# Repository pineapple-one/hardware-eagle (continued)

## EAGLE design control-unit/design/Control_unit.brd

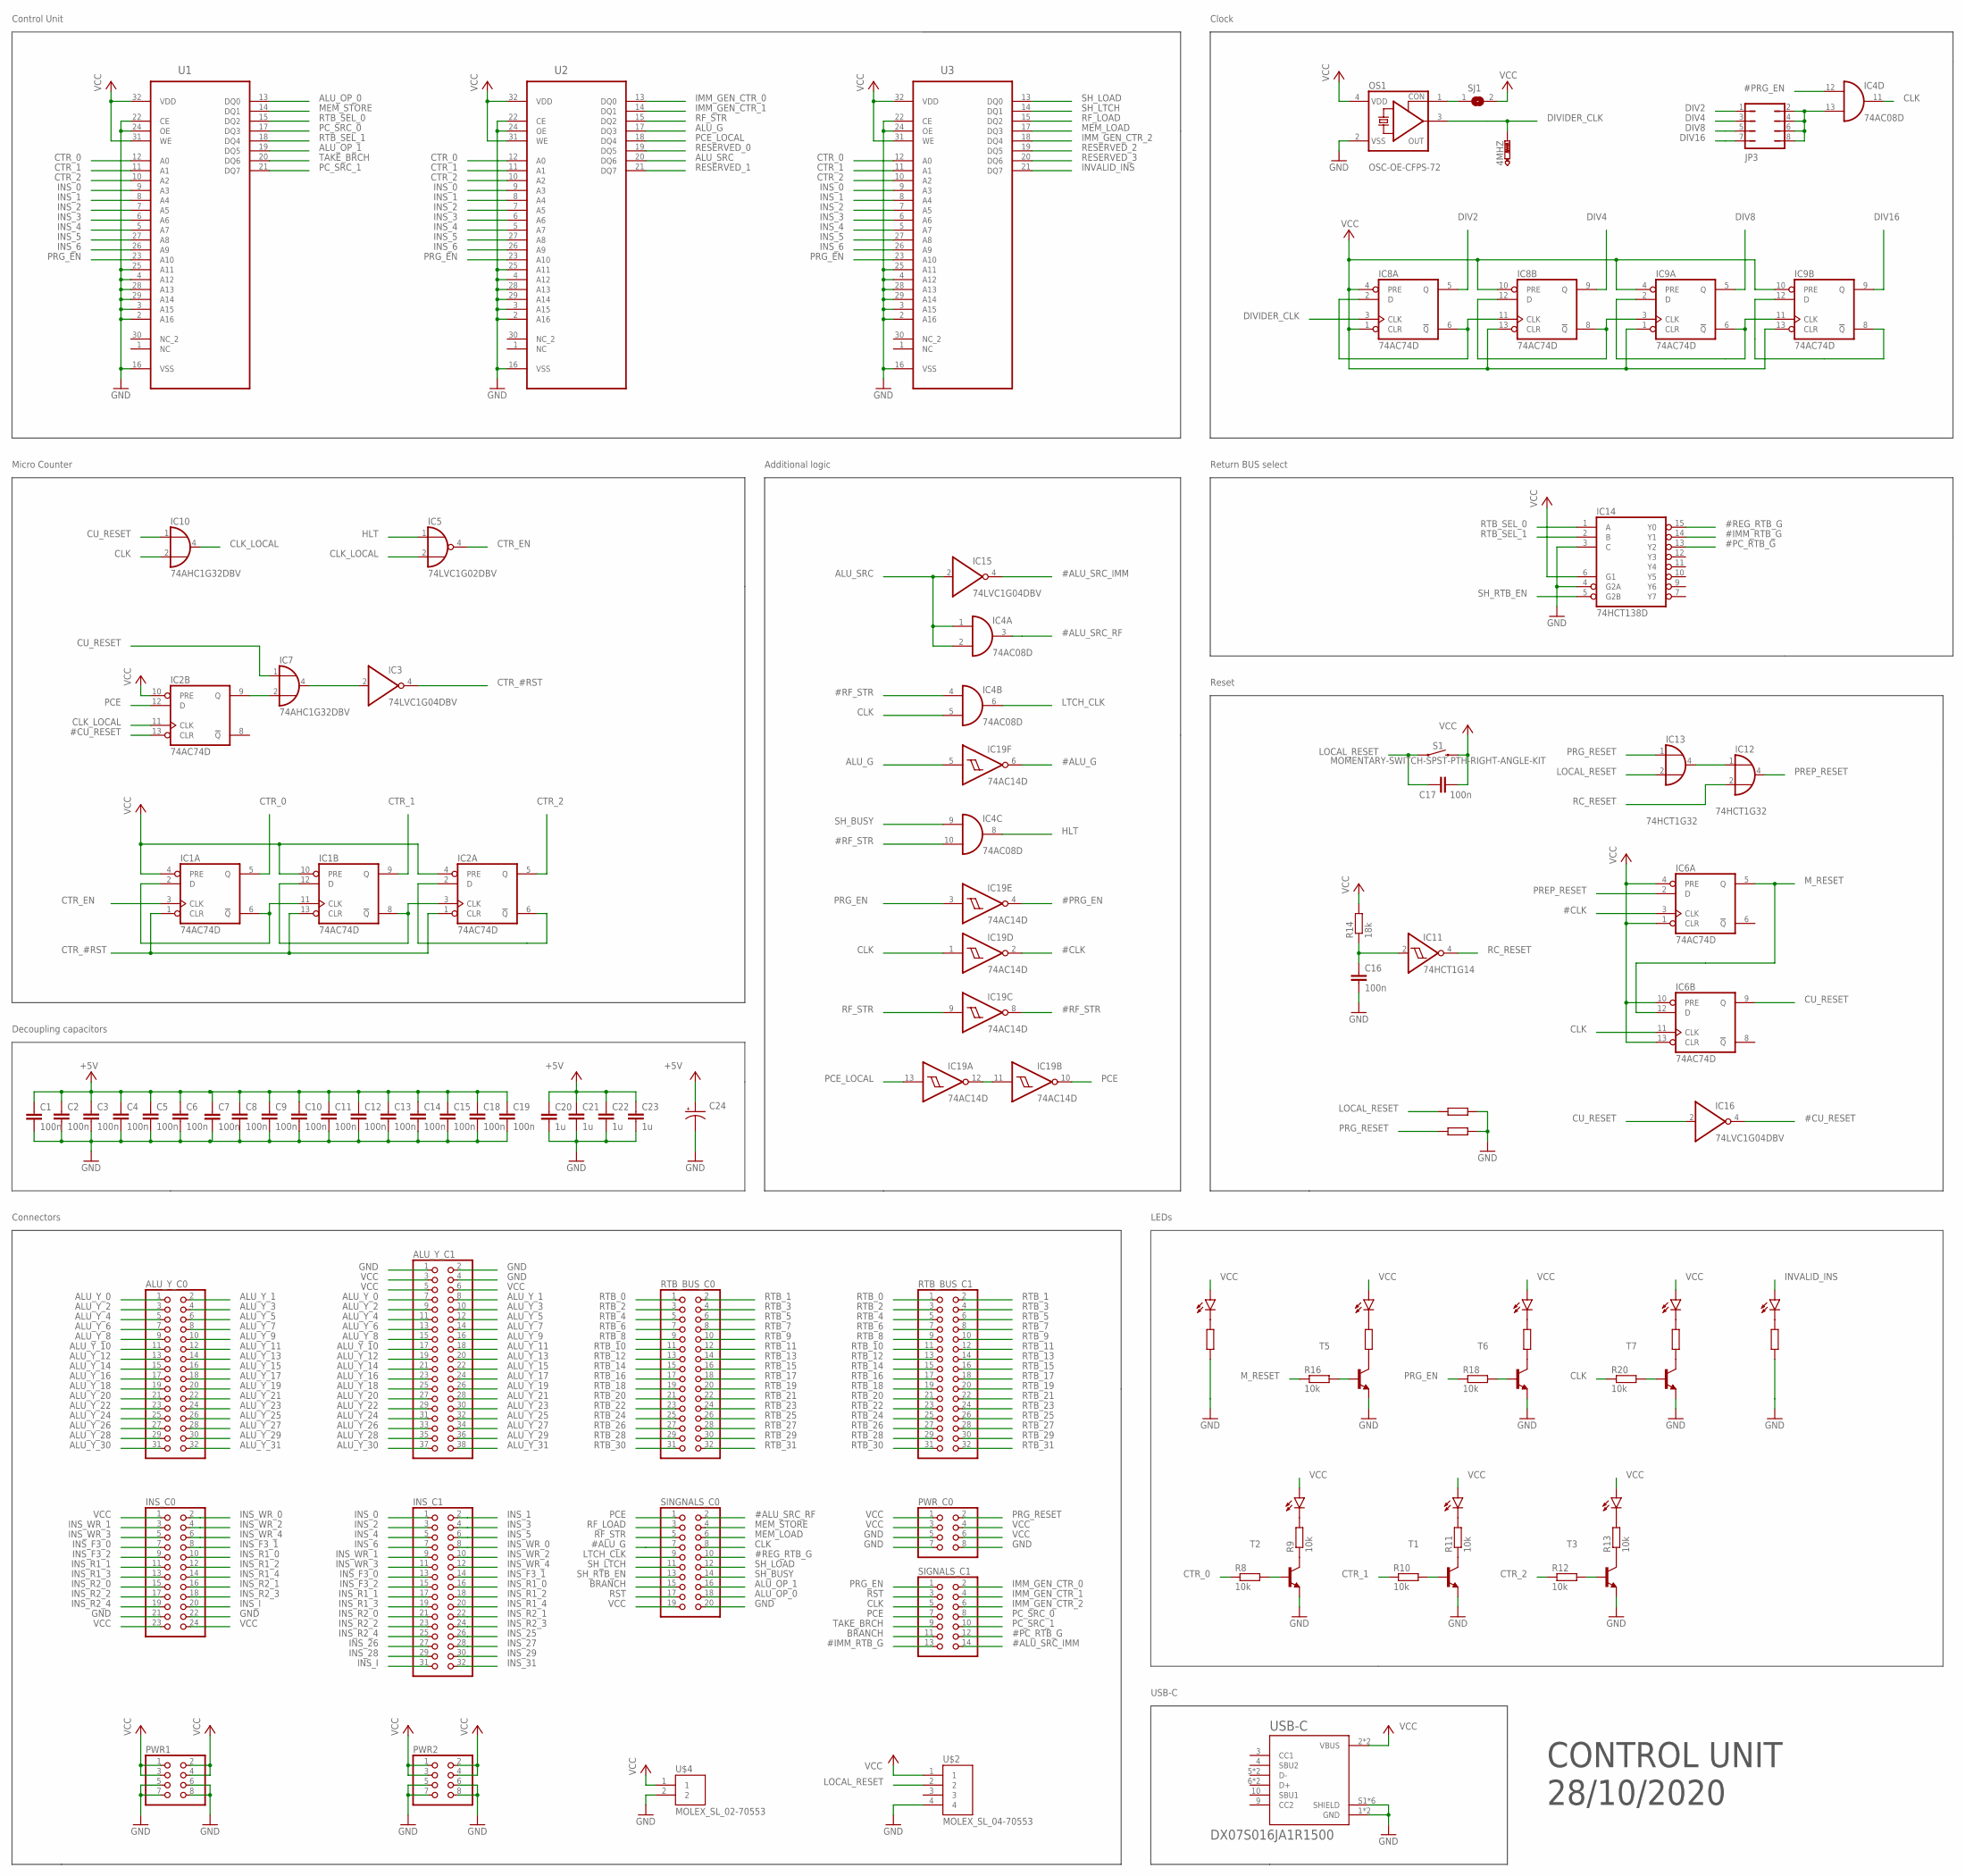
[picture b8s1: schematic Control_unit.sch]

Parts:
4MHZ: PTR1B2,54; B2,54
ALU_Y_C0: PINHD-2X16; 2X16
ALU_Y_C1: PINHD-2X19; 2X19
C1, C2, C3, C4, C5, C6, C7, C8, C9, C10, C11, C12, C13, C14, C15, C16, C17, C18, C19: 100n; C0805
C20, C21, C22, C23: 1u; C0805
C24: CAPACITOR-P153CLV-1010; 153CLV-1010
IC1, IC2, IC6, IC8, IC9: 74AC74D; SO14
IC3, IC15, IC16: 74LVC1G04DBV; SOT23-5
IC4: 74AC08D; SO14
IC5: 74LVC1G02DBV; SOT23-5
IC7, IC10: 74AHC1G32DBV; SOT23-5
IC11: 74HCT1G14; SOT23-5
IC12, IC13: 74HCT1G32; SOT23-5
IC14: 74HCT138D; SO16
IC19: 74AC14D; SO14
INS_C0: PINHD-2X12; 2X12
INS_C1: PINHD-2X16; 2X16
JP3: JP4Q
LED1, LED2, LED3, LED4, LED5, LED6, LED7, LED8: LEDSML0805; SML0805
OS1: OSC-OE-CFPS-72; 7.2X5.2-4-PAD
PWR1, PWR2: PINHD-2X4; 2X04
PWR_C0: PINHD-2X4; 2X04
R1, R2, R8, R9, R10, R11, R12, R13, R16, R18, R20: 10k; M0805
R3, R4, R5, R6, R7: 1k; M0805
R14: 18k; M0805
RTB_BUS_C0, RTB_BUS_C1: PINHD-2X16; 2X16
S1: MOMENTARY-SWITCH-SPST-PTH-RIGHT-ANGLE-KIT; TACTILE_SWITCH_PTH_RIGHT_ANGLE_KIT
SIGNALS_C1: PINHD-2X7; 2X07
SINGNALS_C0: PINHD-2X10; 2X10
SJ1: SJ
T1, T2, T3, T5, T6, T7: MMBT4401LT1-NPN-SOT23-BEC; SOT23-BEC
U1, U2, U3: SST39SF010A-70-4I-NHEPLCC32; S32
U$2: MOLEX_SL_04-70553; SL_70553_4
U$4: MOLEX_SL_02-70553; SL_70553_2
USB-C: DX07S016JA1R1500; JAE_DX07S016JA1R1500

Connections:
#ALU_G: IC19.6 (O), SINGNALS_C0.7
#ALU_SRC_IMM: IC15.4 (O), SIGNALS_C1.14
#ALU_SRC_RF: IC4.3 (O), SINGNALS_C0.2
#CLK: IC6.3 (CLK), IC19.2 (O)
#CU_RESET: IC2.13 (CLR), IC16.4 (O)
#IMM_RTB_G: IC14.14 (Y1), SIGNALS_C1.13
#PC_RTB_G: IC14.13 (Y2), SIGNALS_C1.12
#PRG_EN: IC4.12 (I0), IC19.4 (O)
#REG_RTB_G: IC14.15 (Y0), SINGNALS_C0.10
#RF_STR: IC4.4 (I0), IC4.10 (I1), IC19.8 (O)
ALU_G: IC19.5 (I), U2.17 (DQ3)
ALU_OP_0: SINGNALS_C0.18, U1.13 (DQ0)
ALU_OP_1: SINGNALS_C0.16, U1.19 (DQ5)
ALU_SRC: IC4.1 (I0), IC4.2 (I1), IC15.2 (I), U2.20 (DQ6)
ALU_Y_0: ALU_Y_C0.1, ALU_Y_C1.7
ALU_Y_1: ALU_Y_C0.2, ALU_Y_C1.8
ALU_Y_2: ALU_Y_C0.3, ALU_Y_C1.9
ALU_Y_3: ALU_Y_C0.4, ALU_Y_C1.10
ALU_Y_4: ALU_Y_C0.5, ALU_Y_C1.11
ALU_Y_5: ALU_Y_C0.6, ALU_Y_C1.12
ALU_Y_6: ALU_Y_C0.7, ALU_Y_C1.13
ALU_Y_7: ALU_Y_C0.8, ALU_Y_C1.14
ALU_Y_8: ALU_Y_C0.9, ALU_Y_C1.15
ALU_Y_9: ALU_Y_C0.10, ALU_Y_C1.16
ALU_Y_10: ALU_Y_C0.11, ALU_Y_C1.17
ALU_Y_11: ALU_Y_C0.12, ALU_Y_C1.18
ALU_Y_12: ALU_Y_C0.13, ALU_Y_C1.19
ALU_Y_13: ALU_Y_C0.14, ALU_Y_C1.20
ALU_Y_14: ALU_Y_C0.15, ALU_Y_C1.21
ALU_Y_15: ALU_Y_C0.16, ALU_Y_C1.22
ALU_Y_16: ALU_Y_C0.17, ALU_Y_C1.23
ALU_Y_17: ALU_Y_C0.18, ALU_Y_C1.24
ALU_Y_18: ALU_Y_C0.19, ALU_Y_C1.25
ALU_Y_19: ALU_Y_C0.20, ALU_Y_C1.26
ALU_Y_20: ALU_Y_C0.21, ALU_Y_C1.27
ALU_Y_21: ALU_Y_C0.22, ALU_Y_C1.28
ALU_Y_22: ALU_Y_C0.23, ALU_Y_C1.29
ALU_Y_23: ALU_Y_C0.24, ALU_Y_C1.30
ALU_Y_24: ALU_Y_C0.25, ALU_Y_C1.31
ALU_Y_25: ALU_Y_C0.26, ALU_Y_C1.32
ALU_Y_26: ALU_Y_C0.27, ALU_Y_C1.33
ALU_Y_27: ALU_Y_C0.28, ALU_Y_C1.34
ALU_Y_28: ALU_Y_C0.29, ALU_Y_C1.35
ALU_Y_29: ALU_Y_C0.30, ALU_Y_C1.36
ALU_Y_30: ALU_Y_C0.31, ALU_Y_C1.37
ALU_Y_31: ALU_Y_C0.32, ALU_Y_C1.38
BRANCH: SIGNALS_C1.11, SINGNALS_C0.15
CLK: IC4.5 (I1), IC4.11 (O), IC6.11 (CLK), IC10.2 (I1), IC19.1 (I), R20.1, SIGNALS_C1.5, SINGNALS_C0.8
CLK_LOCAL: IC2.11 (CLK), IC5.2 (I1), IC10.4 (O)
CTR_0: IC1.5 (Q), R8.1, U1.12 (A0), U2.12 (A0), U3.12 (A0)
CTR_1: IC1.9 (Q), R10.1, U1.11 (A1), U2.11 (A1), U3.11 (A1)
CTR_2: IC2.5 (Q), R12.1, U1.10 (A2), U2.10 (A2), U3.10 (A2)
CTR_#RST: IC1.1 (CLR), IC1.13 (CLR), IC2.1 (CLR), IC3.4 (O)
CTR_EN: IC1.3 (CLK), IC5.4 (O)
CU_RESET: IC6.9 (Q), IC7.1 (I0), IC10.1 (I0), IC16.2 (I)
DIV2: IC8.5 (Q), JP3.1
DIV4: IC8.9 (Q), JP3.3
DIV8: IC9.5 (Q), JP3.5
DIV16: IC9.9 (Q), JP3.7
DIVIDER_CLK: 4MHZ.TP, IC8.3 (CLK), OS1.3 (OUT)
GND: ALU_Y_C1.1, ALU_Y_C1.2, ALU_Y_C1.4, C1.2, C2.2, C3.2, C4.2, C5.2, C6.2, C7.2, C8.2, C9.2, C10.2, C11.2, C12.2, C13.2, C14.2, C15.2, C16.2, C18.2, C19.2, C20.2, C21.2, C22.2, C23.2, C24.-, IC1.7 (GND), IC2.7 (GND), IC3.3 (GND), IC4.7 (GND), IC5.3 (GND), IC6.7 (GND), IC7.3 (GND), IC8.7 (GND), IC9.7 (GND), IC10.3 (GND), IC11.3 (GND), IC12.3 (GND), IC13.3 (GND), IC14.3 (C), IC14.4 (G2A), IC14.8 (GND), IC15.3 (GND), IC16.3 (GND), IC19.7 (GND), INS_C0.21, INS_C0.22, OS1.2 (VSS), PWR1.5, PWR1.6, PWR1.7, PWR1.8, PWR2.5, PWR2.6, PWR2.7, PWR2.8, PWR_C0.5, PWR_C0.7, PWR_C0.8, R1.1, R2.1, R3.1, R7.1, SINGNALS_C0.20, T1.E, T2.E, T3.E, T5.E, T6.E, T7.E, U1.2 (A16), U1.3 (A15), U1.4 (A12), U1.16 (VSS), U1.22 (CE), U1.24 (OE), U1.25 (A11), U1.28 (A13), U1.29 (A14), U2.2 (A16), U2.3 (A15), U2.4 (A12), U2.16 (VSS), U2.22 (CE), U2.24 (OE), U2.25 (A11), U2.28 (A13), U2.29 (A14), U3.2 (A16), U3.3 (A15), U3.4 (A12), U3.16 (VSS), U3.22 (CE), U3.24 (OE), U3.25 (A11), U3.28 (A13), U3.29 (A14), U$2.4, U$4.2, USB-C.1 (GND), USB-C.12 (GND), USB-C.S1 (SHIELD), USB-C.S2 (SHIELD), USB-C.S3 (SHIELD), USB-C.S4 (SHIELD), USB-C.S5 (SHIELD), USB-C.S6 (SHIELD)
HLT: IC4.8 (O), IC5.1 (I0)
IMM_GEN_CTR_0: SIGNALS_C1.2, U2.13 (DQ0)
IMM_GEN_CTR_1: SIGNALS_C1.4, U2.14 (DQ1)
IMM_GEN_CTR_2: SIGNALS_C1.6, U3.18 (DQ4)
INS_0: INS_C1.1, U1.9 (A3), U2.9 (A3), U3.9 (A3)
INS_1: INS_C1.2, U1.8 (A4), U2.8 (A4), U3.8 (A4)
INS_2: INS_C1.3, U1.7 (A5), U2.7 (A5), U3.7 (A5)
INS_3: INS_C1.4, U1.6 (A6), U2.6 (A6), U3.6 (A6)
INS_4: INS_C1.5, U1.5 (A7), U2.5 (A7), U3.5 (A7)
INS_5: INS_C1.6, U1.27 (A8), U2.27 (A8), U3.27 (A8)
INS_6: INS_C1.7, U1.26 (A9), U2.26 (A9), U3.26 (A9)
INS_25: INS_C1.26
INS_26: INS_C1.27
INS_27: INS_C1.28
INS_28: INS_C1.29
INS_29: INS_C1.30
INS_31: INS_C1.32
INS_F3_0: INS_C0.7, INS_C1.13
INS_F3_1: INS_C0.8, INS_C1.14
INS_F3_2: INS_C0.9, INS_C1.15
INS_I: INS_C0.20, INS_C1.31
INS_R1_0: INS_C0.10, INS_C1.16
INS_R1_1: INS_C0.11, INS_C1.17
INS_R1_2: INS_C0.12, INS_C1.18
INS_R1_3: INS_C0.13, INS_C1.19
INS_R1_4: INS_C0.14, INS_C1.20
INS_R2_0: INS_C0.15, INS_C1.21
INS_R2_1: INS_C0.16, INS_C1.22
INS_R2_2: INS_C0.17, INS_C1.23
INS_R2_3: INS_C0.18, INS_C1.24
INS_R2_4: INS_C0.19, INS_C1.25
INS_WR_0: INS_C0.2, INS_C1.8
INS_WR_1: INS_C0.3, INS_C1.9
INS_WR_2: INS_C0.4, INS_C1.10
INS_WR_3: INS_C0.5, INS_C1.11
INS_WR_4: INS_C0.6, INS_C1.12
INVALID_INS: LED5.A, U3.21 (DQ7)
LOCAL_RESET: C17.1, IC13.2 (I1), R1.2, S1.1, U$2.2
LTCH_CLK: IC4.6 (O), SINGNALS_C0.9
MEM_LOAD: SINGNALS_C0.6, U3.17 (DQ3)
MEM_STORE: SINGNALS_C0.4, U1.14 (DQ1)
M_RESET: IC6.5 (Q), IC6.12 (D), R16.1
unnamed: IC1.2 (D), IC1.6 (!Q), IC1.11 (CLK)
unnamed: IC12.1 (I0), IC13.4 (O)
unnamed: IC2.9 (Q), IC7.2 (I1)
unnamed: IC3.2 (I), IC7.4 (O)
unnamed: IC19.11 (I), IC19.12 (O)
unnamed: IC8.2 (D), IC8.6 (!Q), IC8.11 (CLK)
unnamed: IC1.8 (!Q), IC1.12 (D), IC2.3 (CLK)
unnamed: R4.1, T5.C
unnamed: IC2.2 (D), IC2.6 (!Q)
unnamed: R5.1, T6.C
unnamed: R6.1, T7.C
unnamed: LED1.C, R3.2
unnamed: R8.2, T2.B
unnamed: LED8.C, R9.2
unnamed: IC8.8 (!Q), IC8.12 (D), IC9.3 (CLK)
unnamed: LED2.C, R4.2
unnamed: LED3.C, R5.2
unnamed: R9.1, T2.C
unnamed: R10.2, T1.B
unnamed: LED6.C, R11.2
unnamed: R11.1, T1.C
unnamed: R12.2, T3.B
unnamed: LED7.C, R13.2
unnamed: R13.1, T3.C
unnamed: R16.2, T5.B
unnamed: LED4.C, R6.2
unnamed: LED5.C, R7.2
unnamed: R18.2, T6.B
unnamed: IC9.2 (D), IC9.6 (!Q), IC9.11 (CLK)
unnamed: IC9.8 (!Q), IC9.12 (D)
unnamed: R20.2, T7.B
unnamed: C16.1, IC11.2 (I), R14.1
unnamed: OS1.1 (CON), SJ1.1
unnamed: IC4.13 (I1), JP3.2, JP3.4, JP3.6, JP3.8
PCE: IC2.12 (D), IC19.10 (O), SIGNALS_C1.7, SINGNALS_C0.1
PCE_LOCAL: IC19.13 (I), U2.18 (DQ4)
PC_SRC_0: SIGNALS_C1.8, U1.17 (DQ3)
PC_SRC_1: SIGNALS_C1.10, U1.21 (DQ7)
PREP_RESET: IC6.2 (D), IC12.4 (O)
PRG_EN: IC19.3 (I), R18.1, SIGNALS_C1.1, U1.23 (A10), U2.23 (A10), U3.23 (A10)
PRG_RESET: IC13.1 (I0), PWR_C0.2, R2.2
RC_RESET: IC11.4 (O), IC12.2 (I1)
RESERVED_0: U2.19 (DQ5)
RESERVED_1: U2.21 (DQ7)
RESERVED_2: U3.19 (DQ5)
RESERVED_3: U3.20 (DQ6)
RF_LOAD: SINGNALS_C0.3, U3.15 (DQ2)
RF_STR: IC19.9 (I), SINGNALS_C0.5, U2.15 (DQ2)
RST: SIGNALS_C1.3, SINGNALS_C0.17
RTB_0: RTB_BUS_C0.1, RTB_BUS_C1.1
RTB_1: RTB_BUS_C0.2, RTB_BUS_C1.2
RTB_2: RTB_BUS_C0.3, RTB_BUS_C1.3
RTB_3: RTB_BUS_C0.4, RTB_BUS_C1.4
RTB_4: RTB_BUS_C0.5, RTB_BUS_C1.5
RTB_5: RTB_BUS_C0.6, RTB_BUS_C1.6
RTB_6: RTB_BUS_C0.7, RTB_BUS_C1.7
RTB_7: RTB_BUS_C0.8, RTB_BUS_C1.8
RTB_8: RTB_BUS_C0.9, RTB_BUS_C1.9
RTB_9: RTB_BUS_C0.10, RTB_BUS_C1.10
RTB_10: RTB_BUS_C0.11, RTB_BUS_C1.11
RTB_11: RTB_BUS_C0.12, RTB_BUS_C1.12
RTB_12: RTB_BUS_C0.13, RTB_BUS_C1.13
RTB_13: RTB_BUS_C0.14, RTB_BUS_C1.14
RTB_14: RTB_BUS_C0.15, RTB_BUS_C1.15
RTB_15: RTB_BUS_C0.16, RTB_BUS_C1.16
RTB_16: RTB_BUS_C0.17, RTB_BUS_C1.17
RTB_17: RTB_BUS_C0.18, RTB_BUS_C1.18
RTB_18: RTB_BUS_C0.19, RTB_BUS_C1.19
RTB_19: RTB_BUS_C0.20, RTB_BUS_C1.20
RTB_20: RTB_BUS_C0.21, RTB_BUS_C1.21
RTB_21: RTB_BUS_C0.22, RTB_BUS_C1.22
RTB_22: RTB_BUS_C0.23, RTB_BUS_C1.23
RTB_23: RTB_BUS_C0.24, RTB_BUS_C1.24
RTB_24: RTB_BUS_C0.25, RTB_BUS_C1.25
RTB_25: RTB_BUS_C0.26, RTB_BUS_C1.26
RTB_26: RTB_BUS_C0.27, RTB_BUS_C1.27
RTB_27: RTB_BUS_C0.28, RTB_BUS_C1.28
RTB_28: RTB_BUS_C0.29, RTB_BUS_C1.29
RTB_29: RTB_BUS_C0.30, RTB_BUS_C1.30
RTB_30: RTB_BUS_C0.31, RTB_BUS_C1.31
RTB_31: RTB_BUS_C0.32, RTB_BUS_C1.32
RTB_SEL_0: IC14.1 (A), U1.15 (DQ2)
RTB_SEL_1: IC14.2 (B), U1.18 (DQ4)
SH_BUSY: IC4.9 (I0), SINGNALS_C0.14
SH_LOAD: SINGNALS_C0.12, U3.13 (DQ0)
SH_LTCH: SINGNALS_C0.11, U3.14 (DQ1)
SH_RTB_EN: IC14.5 (G2B), SINGNALS_C0.13
TAKE_BRCH: SIGNALS_C1.9, U1.20 (DQ6)
VCC: ALU_Y_C1.3, ALU_Y_C1.5, ALU_Y_C1.6, C1.1, C2.1, C3.1, C4.1, C5.1, C6.1, C7.1, C8.1, C9.1, C10.1, C11.1, C12.1, C13.1, C14.1, C15.1, C17.2, C18.1, C19.1, C20.1, C21.1, C22.1, C23.1, C24.+, IC1.4 (PRE), IC1.10 (PRE), IC1.14 (VCC), IC2.4 (PRE), IC2.10 (PRE), IC2.14 (VCC), IC3.5 (VCC), IC4.14 (VCC), IC5.5 (VCC), IC6.1 (CLR), IC6.4 (PRE), IC6.10 (PRE), IC6.13 (CLR), IC6.14 (VCC), IC7.5 (VCC), IC8.1 (CLR), IC8.4 (PRE), IC8.10 (PRE), IC8.13 (CLR), IC8.14 (VCC), IC9.1 (CLR), IC9.4 (PRE), IC9.10 (PRE), IC9.13 (CLR), IC9.14 (VCC), IC10.5 (VCC), IC11.5 (VCC), IC12.5 (VCC), IC13.5 (VCC), IC14.6 (G1), IC14.16 (VCC), IC15.5 (VCC), IC16.5 (VCC), IC19.14 (VCC), INS_C0.1, INS_C0.23, INS_C0.24, LED1.A, LED2.A, LED3.A, LED4.A, LED6.A, LED7.A, LED8.A, OS1.4 (VDD), PWR1.1, PWR1.2, PWR1.3, PWR1.4, PWR2.1, PWR2.2, PWR2.3, PWR2.4, PWR_C0.1, PWR_C0.3, PWR_C0.4, PWR_C0.6, R14.2, S1.2, SINGNALS_C0.19, SJ1.2, U1.31 (WE), U1.32 (VDD), U2.31 (WE), U2.32 (VDD), U3.31 (WE), U3.32 (VDD), U$2.1, U$4.1, USB-C.2 (VBUS), USB-C.11 (VBUS)

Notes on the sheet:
Control Unit
Micro Counter
Reset
Return BUS select
Connectors
Clock
Decoupling capacitors
LEDs
Additional logic
USB-C
CONTROL UNIT 28/10/2020

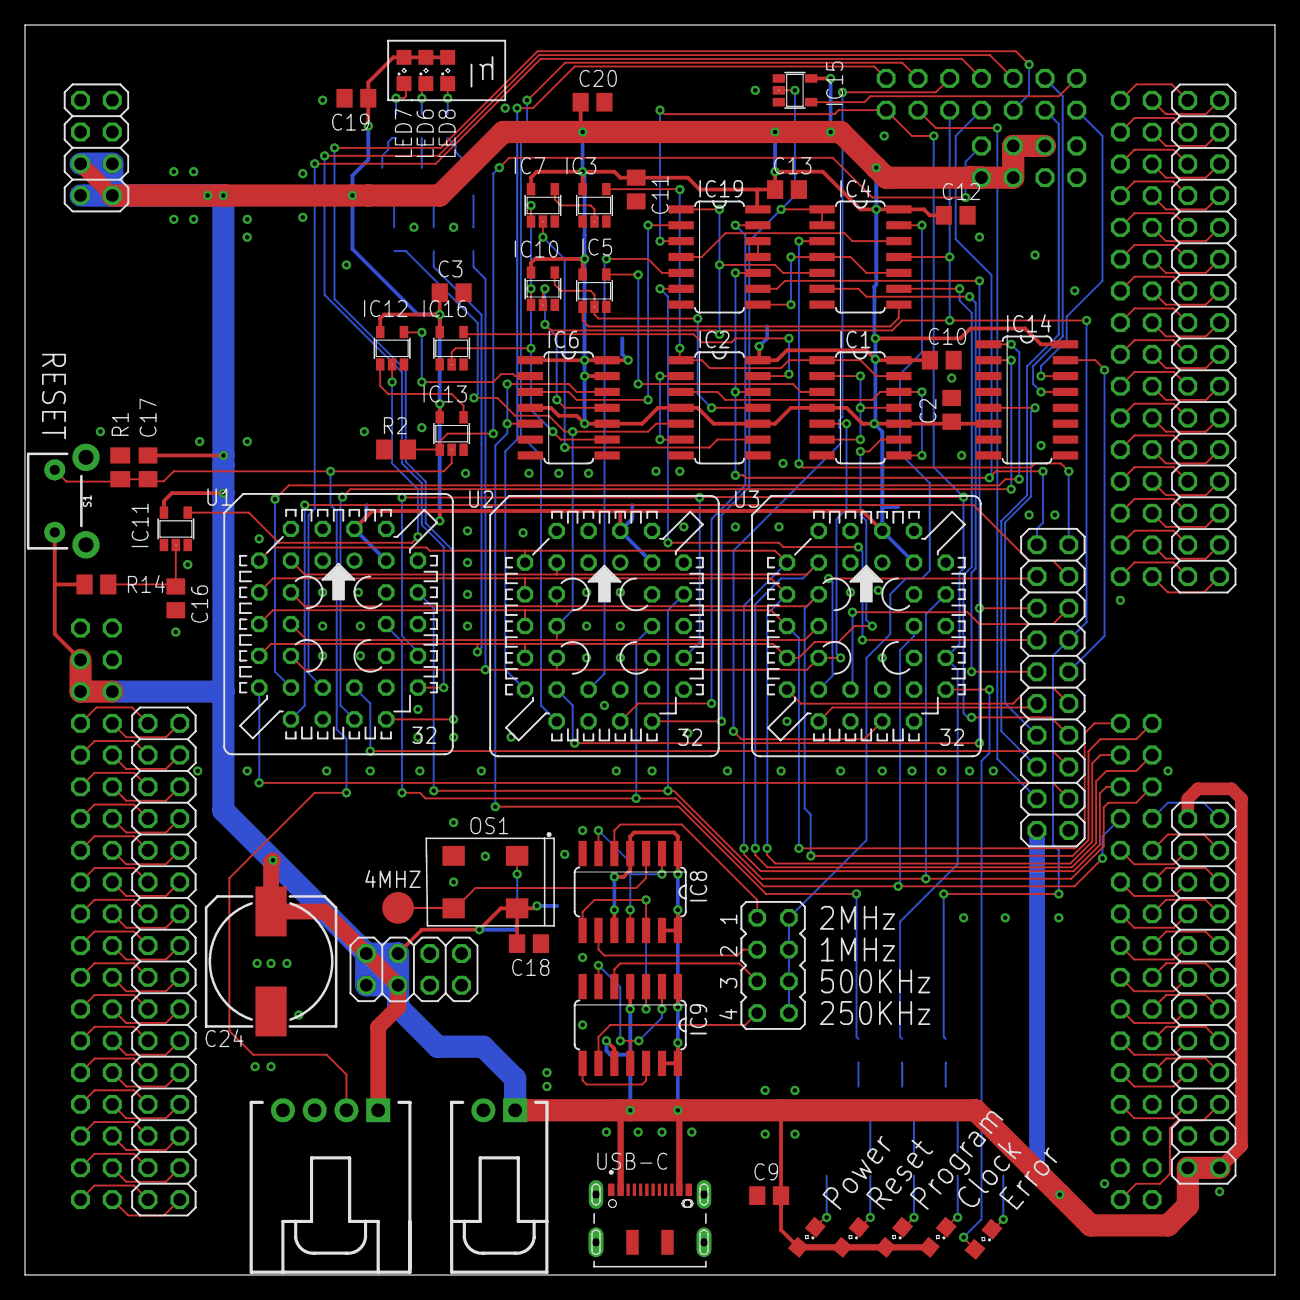
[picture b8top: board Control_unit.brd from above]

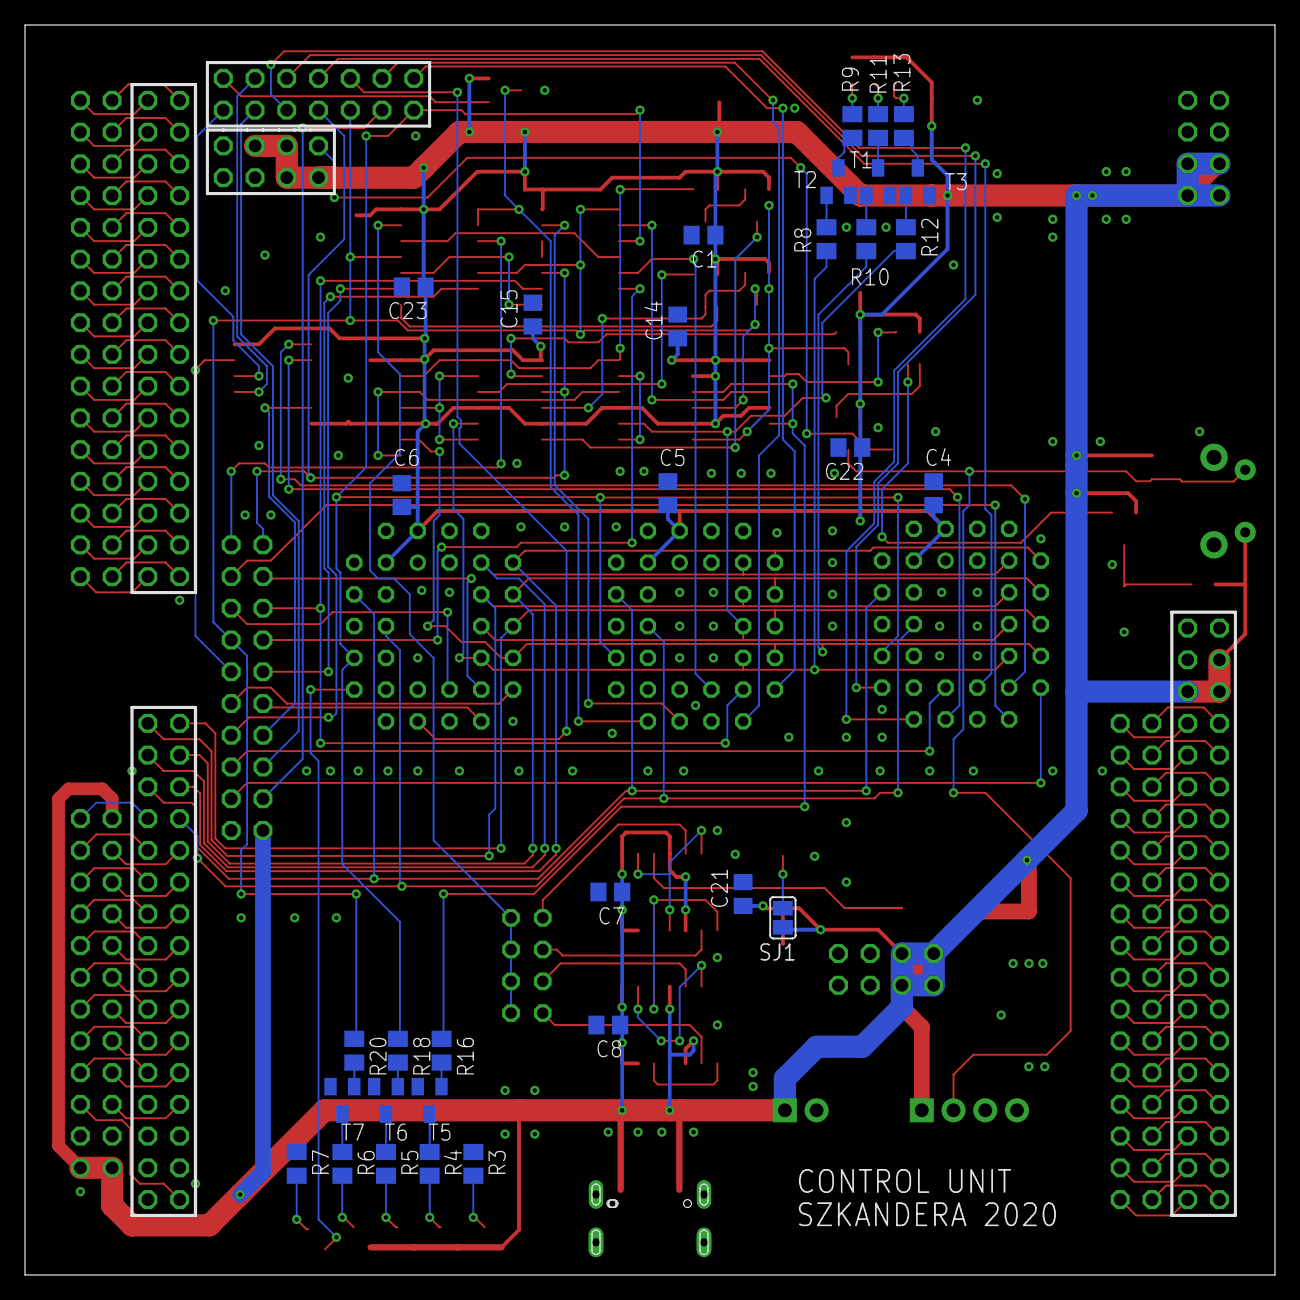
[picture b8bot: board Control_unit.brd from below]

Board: 2 copper layers, 100.0 x 100.0 mm, 94 parts (32 on the bottom side), 182 nets.

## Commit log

2021-05-21 Added ALU module
2021-05-21 Added Control unit module
2021-05-21 Added VGA card module
2021-05-21 Added Instruction memory module
2021-05-21 Added Program counter module
2021-05-21 Added RAM module
2021-05-21 Added Register file module
2021-05-21 Added Shifter module
2021-05-21 Added Transport layer module
2021-05-21 Added EEPROM values
